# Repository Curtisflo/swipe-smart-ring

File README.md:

# Swipe Smart Ring — Ring PCB

The main board for a BLE smart ring with IMU-based gesture input and capacitive
touch. This repo contains the **ring board** KiCad project: PCB layout,
schematic, and the custom footprints used by both.

**Status:** prototype, not yet fabricated or tested. Routed and verified in
KiCad 9 — **DRC clean: 0 errors, 0 warnings, 0 unconnected nets.**

It's small — the board outline is **38 × 10 mm** (about the footprint of a
stick of gum).

The board isn't meant to stay flat. The middle 8 mm is a **flex** section: the
rigid signet and BLE ends fold relative to each other there, so the board follows
the curve of the finger inside the housing. In the housing the BLE end sits
**115°** around the ring from the signet, and the rigid ends stay flat — so the
8 mm flex takes that whole ~115° bend (about a 4 mm radius, well inside the
material's 0.6 mm minimum).

A note on the rigid-flex: the flex zone is captured here as **design intent** —
the layout is zoned signet (18 mm) / flex (8 mm) / BLE (12 mm) along the board's
length, with the bend taken by the middle 8 mm. The `ring.kicad_pcb` itself is a
flat 2-layer prototype; the actual rigid-flex **stackup and coverlay callouts are
left to the fabricator**.

## What this is

A 2-layer **rigid-flex** board that wraps around a finger. It carries a Nordic
nRF52832 BLE SoC, a 6-axis IMU with built-in capacitive (Qvar) touch sensing, a
haptic motor driver, indicator LEDs, and the spring contacts / connectors that
mate with the ring housing.

The board is split into three zones along its length:

```
[ signet  18mm rigid ] —— [ flex 8mm ] —— [ BLE 12mm rigid ]
  battery + motor +                          ANNA-B112 module +
  LED arc + drivers                          antenna keepout + SWD
```

- **Signet** (rigid): battery and motor spring contacts, the two bicolor
  indicator LEDs (light-pipe aligned), the motor MOSFET and flyback diode, and
  the electrode-harness connector.
- **Flex**: the bend region that lets the rigid ends curve around the finger.
- **BLE** (rigid): the ANNA-B112 module with an antenna keepout, plus the SWD
  programming pads and the pogo-harness connector.

## Key components

| Ref | Part | Function |
|-----|------|----------|
| U1  | u-blox **ANNA-B112** (nRF52832) | BLE SoC module, pre-certified, integrated antenna |
| U2  | ST **LSM6DSV16X** | 6-axis IMU + **Qvar** capacitive touch, LGA-14 |
| Q1  | Infineon IRLML6344 | N-ch MOSFET, haptic motor low-side drive |
| D1  | Vishay BAT54W | Schottky motor flyback clamp |
| D2, D3 | American Bright BL-HG0E136J | Bicolor indicator LEDs |
| ESD1/2 | ST ESDALCL5-1BM2 | ESD protection on the Qvar electrode lines |
| J1  | Molex 5034800240 | 2-pin FPC — pogo/charge harness (VBUS, GND) |
| J2  | Molex 5034800440 | 4-pin FPC — electrode harness (Qvar×2, GND×2) |
| SP1–SP4 | KYOCERA AVX 70-9155 | Spring contacts — battery (×2) and motor (×2) |

Full line-item list (passives, MPNs, prices) in [`bom.csv`](bom.csv). The
battery (Seiko MS920SE coin cell) and haptic motor are off-board — they sit in
the housing and contact the spring pads — and are listed at the end of the BOM.

## Design notes

- **No LDO.** VDD = VBAT throughout — the nRF52832 (1.7–3.6 V) runs directly
  off the coin cell (Seiko MS920SE, ~2.0–3.1 V).
- **Motor** runs off the battery rail directly, switched by Q1.
- **Qvar touch** uses the IMU's analog-front-end inputs through 500 Ω series
  resistors, with ESD diodes at the connector.
- **Charging** is resistor-limited from a 5 V pogo input (R3 = 2.2 kΩ →
  ~0.86 mA into the MS920).
- **Layers, not vias.** The fine-pitch parts (ANNA's inner pads, the LSM6DSV16X)
  are fanned out on 2 layers rather than escalating to 4-layer / via-in-pad.
  Vias are 0.3 mm (0.15 mm drill) — standard fab capability, sized so the
  LSM6DSV16X's 0.5 mm-pitch escapes clear the 0.127 mm rule.

The full product also includes a pogo charge-contact board, a Qvar electrode
flex, and a USB-C dock — those are not part of this repo.

## Opening it

Built with **KiCad 9**. Clone and open `ring.kicad_pro`, or open
`ring.kicad_pcb` / `ring.kicad_sch` directly. Footprints are embedded in the
board, and the `custom.pretty` library is included for editing.

- `ring.kicad_pcb` — routed PCB layout
- `ring.kicad_sch` — schematic
- `ring.kicad_pro` — KiCad project
- `custom.pretty/` — custom footprints
- `bom.csv` — bill of materials for this board
- `ring-schematic.pdf` — schematic as a PDF (no KiCad needed)
- `preview.png` — rendered board, top and bottom (KiCad 9, 38 × 10 mm)
- `preview-3d.png` — 3D view of the rigid-flex fold at the flex zone
- `fab/` — Gerbers and Excellon drill files (KiCad 9 export), ready to order

## License

MIT — see [LICENSE](LICENSE).

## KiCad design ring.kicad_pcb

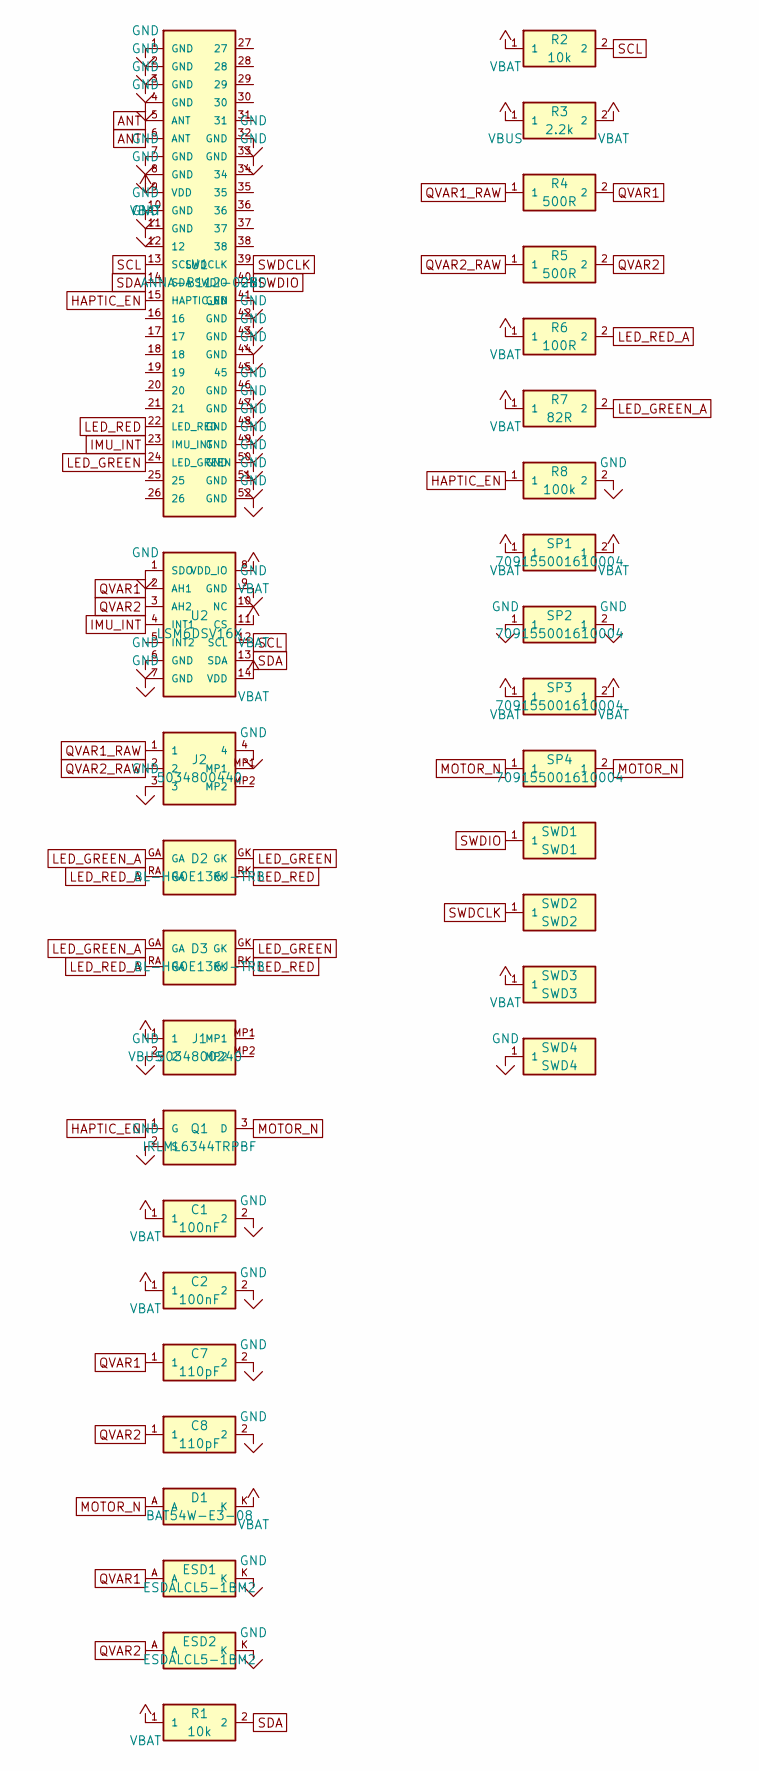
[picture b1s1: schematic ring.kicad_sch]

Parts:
C1, C2: 100nF; R_0402_1005Metric
C7, C8: 110pF; R_0402_1005Metric
D1: BAT54W-E3-08; D_SOD-123
D2, D3: BL-HG0E136J-TRB; LED_0605_BiColor
ESD1, ESD2: ESDALCL5-1BM2; D_SOD-882
J1: 5034800240; Molex_503480_2pin
J2: 5034800440; Molex_503480_4pin
Q1: IRLML6344TRPBF; SOT-23
R1, R2: 10k; R_0402_1005Metric
R3: 2.2k; R_0402_1005Metric
R4, R5: 500R; R_0402_1005Metric
R6: 100R; R_0402_1005Metric
R7: 82R; R_0402_1005Metric
R8: 100k; R_0402_1005Metric
SP1, SP2, SP3, SP4: 709155001610004; AVX_9155_Battery_Contact
SWD1: SWD1; Pad_1.0x1.0mm
SWD2: SWD2; Pad_1.0x1.0mm
SWD3: SWD3; Pad_1.0x1.0mm
SWD4: SWD4; Pad_1.0x1.0mm
U1: ANNA-B112-02B; ANNA-B112
U2: LSM6DSV16X; LGA-14_2.5x3mm_P0.5mm_LSM6DSV16X

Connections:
ANT: U1.5 (ANT), U1.6 (ANT)
GND: C1.2, C2.2, C7.2, C8.2, ESD1.K, ESD2.K, J1.2, J2.3, J2.4, Q1.2 (S), R8.2, SP2.1, SP2.2, SWD4.1, U1.1 (GND), U1.2 (GND), U1.3 (GND), U1.4 (GND), U1.7 (GND), U1.8 (GND), U1.10 (GND), U1.11 (GND), U1.32 (GND), U1.33 (GND), U1.41 (GND), U1.42 (GND), U1.43 (GND), U1.44 (GND), U1.46 (GND), U1.47 (GND), U1.48 (GND), U1.49 (GND), U1.50 (GND), U1.51 (GND), U1.52 (GND), U2.1 (SDO), U2.6 (GND), U2.7 (GND), U2.9 (GND)
HAPTIC_EN: Q1.1 (G), R8.1, U1.15 (HAPTIC_EN)
IMU_INT: U1.23 (IMU_INT), U2.4 (INT1)
LED_GREEN: D2.GK, D3.GK, U1.24 (LED_GREEN)
LED_GREEN_A: D2.GA, D3.GA, R7.2
LED_RED: D2.RK, D3.RK, U1.22 (LED_RED)
LED_RED_A: D2.RA, D3.RA, R6.2
MOTOR_N: D1.A, Q1.3 (D), SP4.1, SP4.2
QVAR1: C7.1, ESD1.A, R4.2, U2.2 (AH1)
QVAR1_RAW: J2.1, R4.1
QVAR2: C8.1, ESD2.A, R5.2, U2.3 (AH2)
QVAR2_RAW: J2.2, R5.1
SCL: R2.2, U1.13 (SCL), U2.12 (SCL)
SDA: R1.2, U1.14 (SDA), U2.13 (SDA)
SWDCLK: SWD2.1, U1.39 (SWDCLK)
SWDIO: SWD1.1, U1.40 (SWDIO)
VBAT: C1.1, C2.1, D1.K, R1.1, R2.1, R3.2, R6.1, R7.1, SP1.1, SP1.2, SP3.1, SP3.2, SWD3.1, U1.9 (VDD), U2.8 (VDD_IO), U2.11 (CS), U2.14 (VDD)
VBUS: J1.1, R3.1

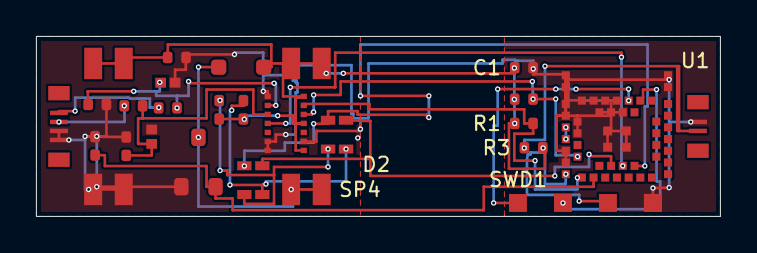
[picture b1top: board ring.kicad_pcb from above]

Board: 2 copper layers, 38.0 x 10.0 mm, 30 parts (0 on the bottom side), 19 nets.
